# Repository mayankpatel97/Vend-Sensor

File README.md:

Vend sensor is used to detect an item has vend in Vending Machines. It sense the product and send a signal to 
the main motherboard, indicating item has vend. Responding to this signal motherboard will stop rotating motor

Every vending machine has a rectangular bucket from where user collects the purchased items. This sensor will 
be installed there, so it can detect and count each and every product dropped by machine in to the bucket.

A vend sensor must be sensitive and fast enough to detect even tiny products. 

The product has two pcbs 
1) Transmitter : An array IR LEDs transmitting a 56Khz modulated signal. This pcb is connected with Receiver board through a cable
2) Receiver : This board consist of IR demodulators connected to an STM32F0 microcontroller.

************************** PCB ****************************************
Receiver PCB 

Transmitter PCB 

************************* Software *************************************

As I mentioned above the circuit is built around STM32F0 microcontroller, it uses HAL drivers.
Follow below steps to make the code working 

1) Download the code and open STM32 Cube file and regenerate the code.
2) Once the code has generated, open the project in keil MDK ARM, and build the code.
3) Then upload the code in the microcontroller. 

for further details contact me at 
mayankpatel468@gmail.com 
or send a whatsapp message on 
+918802846486

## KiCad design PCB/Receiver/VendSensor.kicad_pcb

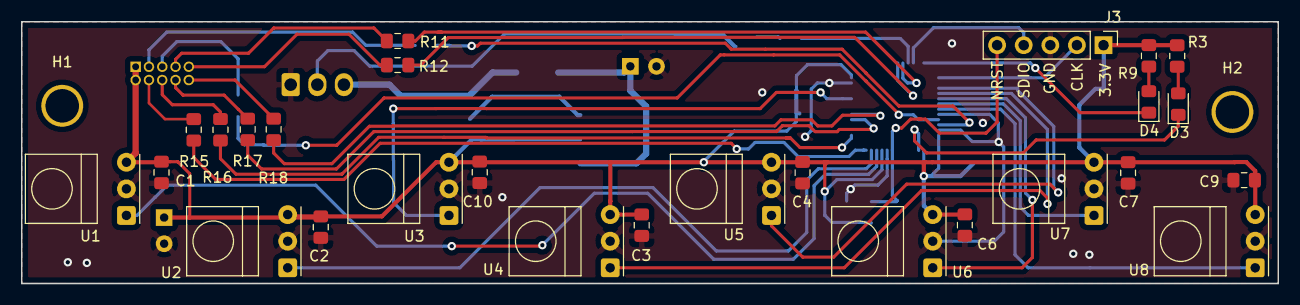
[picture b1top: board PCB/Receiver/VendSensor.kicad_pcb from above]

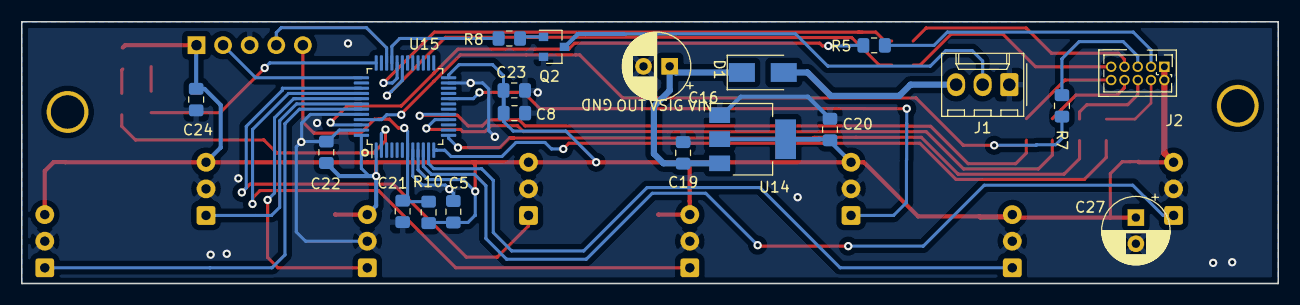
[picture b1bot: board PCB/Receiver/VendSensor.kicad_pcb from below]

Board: 2 copper layers, 120.0 x 25.0 mm, 49 parts (20 on the bottom side), 38 nets.

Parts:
C1, C2, C3, C4, C5, C6, C7, C8, C19, C20, C21, C22, C23, C24: 0.1uF; C_0805_2012Metric_Pad1.15x1.40mm_HandSolder
C9, C10: 10uF; C_0805_2012Metric_Pad1.15x1.40mm_HandSolder
C16, C27: 100uF/25V; CP_Radial_D6.3mm_P2.50mm
D1: M7; D_SMA
D3: GREEN; LED_0805_2012Metric_Pad1.15x1.40mm_HandSolder
D4: YELLOW; LED_0805_2012Metric_Pad1.15x1.40mm_HandSolder
H1, H2: MountingHole; MountingHole_3.2mm_M3_Pad
J1: Conn_01x03; Molex_KK-254_AE-6410-03A_1x03_P2.54mm_Vertical
J2: Conn_02x05_Odd_Even; PinHeader_2x05_P1.27mm_Vertical
J3: Conn_01x05; PinHeader_1x05_P2.54mm_Vertical
Q2: BC847; SOT-23
R3, R9: 330E; R_0805_2012Metric_Pad1.15x1.40mm_HandSolder
R5, R7, R11, R12, R15, R16, R17, R18: 100E; R_0805_2012Metric_Pad1.15x1.40mm_HandSolder
R8: 1K; R_0805_2012Metric_Pad1.15x1.40mm_HandSolder
R10: 10K; R_0805_2012Metric_Pad1.15x1.40mm_HandSolder
U1, U2, U3, U4, U5, U6, U7, U8: TSSP4056; tssp4056
U14: LD1117S33TR_SOT223; SOT-223-3_TabPin2
U15: STM32F030C8Tx; LQFP-48_7x7mm_P0.5mm

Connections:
+3V3: C1.1, C2.1, C3.1, C4.1, C5.1, C6.1, C7.1, C8.1, C9.1, C10.1, C20.1, C22.1, C23.1, C24.1, C27.1, J2.1, J2.2, J3.1, R3.1, R9.1, R10.1, U1.3, U2.3, U3.3, U4.3, U5.3, U6.3, U7.3, U8.3, U14.2, U15.1, U15.9, U15.24, U15.48
GND: C1.2, C2.2, C3.2, C4.2, C5.2, C6.2, C7.2, C8.2, C9.2, C10.2, C16.2, C19.2, C20.2, C21.2, C22.2, C23.2, C24.2, C27.2, J1.1, J3.3, Q2.2, U1.2, U2.2, U3.2, U4.2, U5.2, U6.2, U7.2, U8.2, U14.1, U15.8, U15.23, U15.44, U15.47
GREEN: D3.1, U15.2
IR1: U1.1, U15.10
IR2: U2.1, U15.11
IR3: U3.1, U15.20
IR4: U5.1, U15.39
IR5: U4.1, U15.40
IR6: U6.1, U15.41
IR7: U7.1, U15.42
IR8: U8.1, U15.43
IRLED1: R5.2, U15.46
IRLED2: R15.1, U15.12
IRLED3: R7.2, U15.45
IRLED4: R16.1, U15.13
IRLED5: R11.2, U15.32
IRLED6: R17.1, U15.16
IRLED7: R12.2, U15.31
IRLED8: R18.1, U15.17
NRST: C21.1, J3.5, R10.2, U15.7
unnamed: C16.1, C19.1, D1.1, U14.3
unnamed: D1.2, J1.3
unnamed: D3.2, R3.2
unnamed: D4.2, R9.2
unnamed: J2.3, R5.1
unnamed: J2.4, R15.2
unnamed: J2.5, R7.1
unnamed: J2.6, R16.2
unnamed: J2.7, R11.1
unnamed: J2.8, R17.2
unnamed: J2.9, R12.1
unnamed: J2.10, R18.2
unnamed: Q2.1, R8.2
OUT: R8.1, U15.33
OUTPUT: J1.2, Q2.3
SWCLK: J3.2, U15.37
SWDIO: J3.4, U15.34
YELLOW: D4.1, U15.36

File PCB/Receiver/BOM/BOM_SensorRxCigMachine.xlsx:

S.No | Designator | Value | Description | QTY
1 | > C1-C8, C19-C24 | 0.1uF | Capacitor_SMD:C_0805_2012Metric_Pad1.15x1.40mm_HandSolder | 14
2 | > C9, C10 | 10uF | Capacitor_SMD:C_0805_2012Metric_Pad1.15x1.40mm_HandSolder | 2
3 | > C16, C27 | 100uF/25V | Capacitor_THT:CP_Radial_D6.3mm_P2.50mm | 2
4 | D1 | M7 | Diode_SMD:D_SMA | 1
5 | D3 | GREEN | LED_SMD:LED_0805_2012Metric_Pad1.15x1.40mm_HandSolder | 1
6 | D4 | YELLOW | LED_SMD:LED_0805_2012Metric_Pad1.15x1.40mm_HandSolder | 1
7 | > H1, H2 | MountingHole | MountingHole:MountingHole_3.2mm_M3_Pad | 2
8 | J1 | Conn_01x03 | Connector_Molex:Molex_KK-254_AE-6410-03A_1x03_P2.54mm_Vertical | 1
9 | J2 | Conn_02x05_Odd_Even | Connector_PinHeader_1.27mm:PinHeader_2x05_P1.27mm_Vertical | 1
10 | J3 | Conn_01x05 | Connector_PinHeader_2.54mm:PinHeader_1x05_P2.54mm_Vertical | 1
11 | Q2 | BC847 | Package_TO_SOT_SMD:SOT-23 | 1
12 | > R3, R9 | 330E | Resistor_SMD:R_0805_2012Metric_Pad1.15x1.40mm_HandSolder | 2
13 | > R5, R7, R11, R12, R15-R18 | 100E | Resistor_SMD:R_0805_2012Metric_Pad1.15x1.40mm_HandSolder | 8
14 | R8 | 1K | Resistor_SMD:R_0805_2012Metric_Pad1.15x1.40mm_HandSolder | 1
15 | R10 | 10K | Resistor_SMD:R_0805_2012Metric_Pad1.15x1.40mm_HandSolder | 1
16 | > U1-U8 | TSSP4056 | Apogee:tssp4056 | 8
17 | U14 | LD1117S33TR_SOT223 | Package_TO_SOT_SMD:SOT-223-3_TabPin2 | 1
18 | U15 | STM32F030C8Tx | Package_QFP:LQFP-48_7x7mm_P0.5mm | 1

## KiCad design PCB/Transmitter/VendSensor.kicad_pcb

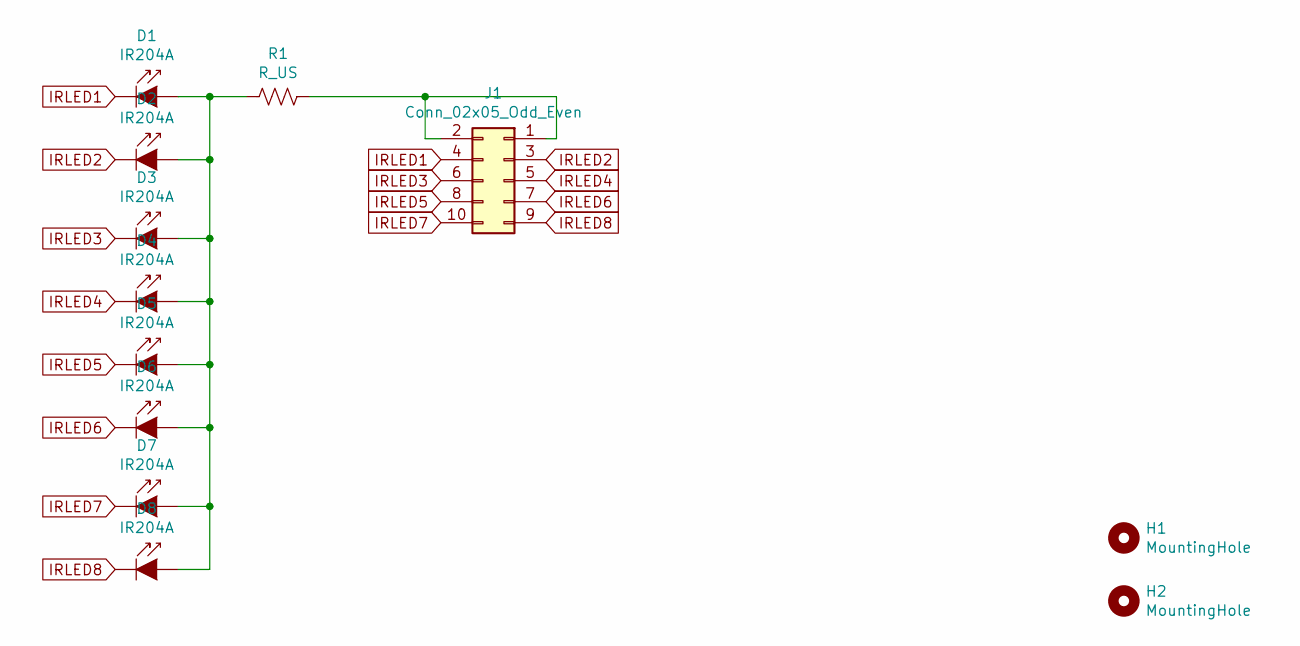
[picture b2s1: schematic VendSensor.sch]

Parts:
D1, D2, D3, D4, D5, D6, D7, D8: IR204A; LED_D5.0mm_IRBlack
H1, H2: MountingHole; MountingHole_3.2mm_M3_Pad
J1: Conn_02x05_Odd_Even; PinSocket_2x05_P1.27mm_Vertical
R1: R_US; LED_0805_2012Metric_Pad1.15x1.40mm_HandSolder

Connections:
IRLED1: D1.1 (K), J1.4
IRLED2: D2.1 (K), J1.3
IRLED3: D3.1 (K), J1.6
IRLED4: D4.1 (K), J1.5
IRLED5: D5.1 (K), J1.8
IRLED6: D6.1 (K), J1.7
IRLED7: D7.1 (K), J1.10
IRLED8: D8.1 (K), J1.9
unnamed: D1.2 (A), D2.2 (A), D3.2 (A), D4.2 (A), D5.2 (A), D6.2 (A), D7.2 (A), D8.2 (A), R1.2
unnamed: J1.1, J1.2, R1.1

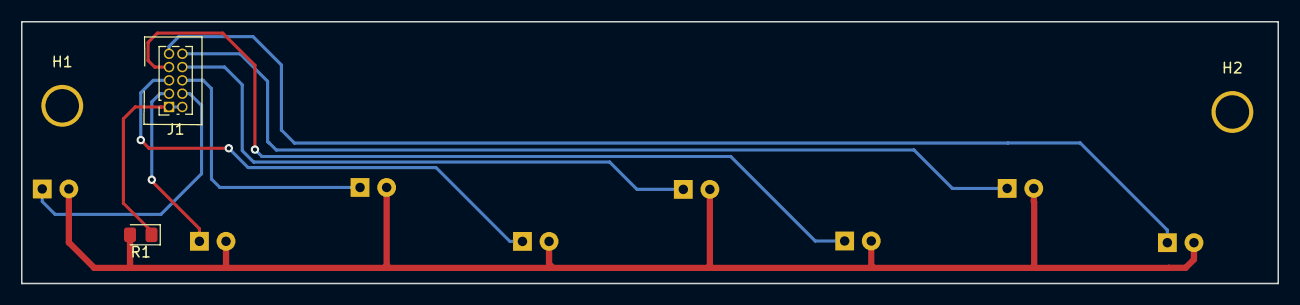
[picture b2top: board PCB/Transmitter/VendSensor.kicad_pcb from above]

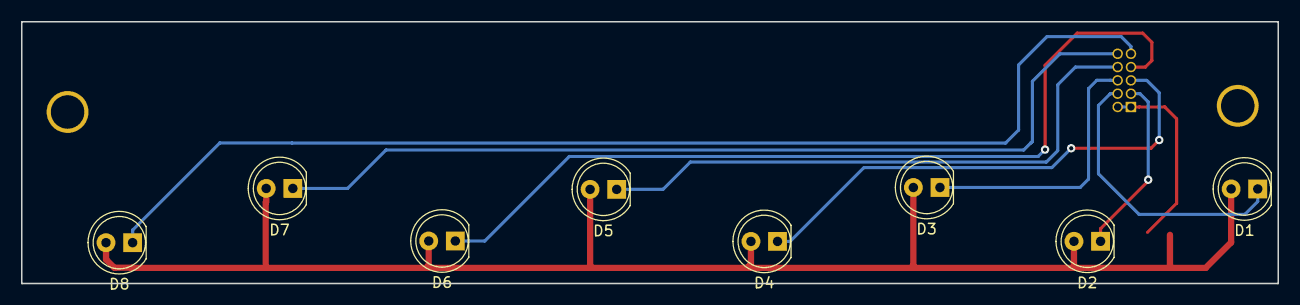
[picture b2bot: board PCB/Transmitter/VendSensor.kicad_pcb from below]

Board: 2 copper layers, 120.0 x 25.0 mm, 12 parts (8 on the bottom side), 10 nets.

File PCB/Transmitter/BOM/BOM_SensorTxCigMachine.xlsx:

S.No | Designator | Value | Description | QTY
1 | D1-D8 | IR204A | LED_THT:LED_D5.0mm_IRBlack | 8
2 | H1, H2 | MountingHole | MountingHole:MountingHole_3.2mm_M3_Pad | 2
3 | J1 | Conn_02x05_Odd_Even | Connector_PinSocket_1.27mm:PinSocket_2x05_P1.27mm_Vertical | 1
4 | R1 | R_US | LED_SMD:LED_0805_2012Metric_Pad1.15x1.40mm_HandSolder | 1
